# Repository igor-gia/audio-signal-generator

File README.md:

# AGP-S3: Dual-Channel Audio Generator & SD Player

[English](#english) | [Українська](#ukrainian) | [русский](#russian)

---

## English

**AGP-S3** is a compact dual-channel low-frequency DDS signal generator and audio player for lossless and high-resolution audio files. The device is based on an **ESP32-S3** microcontroller and a dedicated stereo **PCM5102A** DAC supporting up to 192 kHz / 24-bit audio.

The instrument is intended for testing, adjustment, and repair of audio equipment, including power amplifiers, loudspeakers, crossovers, equalizers, and other stages in the audio signal path.

---

## 📝 Author's Preface and Project Backstory

The idea for this device came from a practical problem encountered while building a home media centre based on an ESP32 and TPA3255, and assembling a custom 10-inch subwoofer using an Alpine driver and a TPA3255 monoblock in parallel bridge-tied load (PBTL) mode.

I had a portable FNIRSI DSO-TC4 on the bench, combining an oscilloscope and a signal generator. Both instruments share a common circuit ground. When adjusting an amplifier operating in bridge mode (BTL/PBTL), it is therefore not possible to apply a test signal to the input and measure the output with the oscilloscope at the same time: the test equipment would connect one output phase to ground.

The initial plan was to build a simple standalone sine-wave generator from the parts available. Since an **ESP32-S3 (N16R8)** was available, the project developed into a more complete instrument.

The result is a laboratory instrument covering two applications:
1. **Audio-equipment adjustment:** a dual-channel pure-tone generator, phase shifter, and test-noise source with galvanically isolated outputs for use with an oscilloscope.
2. **Audio playback:** a standalone player for lossless audio files that can be used as a reference source when evaluating audio signal paths.

Many DIY generators use the microcontroller's internal DACs or PWM output. Depending on the implementation, these can introduce significant distortion and unwanted spectral components. The **AGP-S3** uses a dedicated **PCM5102A** stereo DAC connected through I2S. The ESP32-S3 performs the phase and frequency calculations in real time.

---

## 🚀 Key Features

* **Dual-core operation:** Audio generation and I2S servicing run on one ESP32-S3 core, while the user interface, button handling, and SD-card access run on the other.
* **Audio output:** The PCM5102A provides an analogue output with sample rates up to 192 kHz and 24-bit samples.
* **Dual-channel DDS generator:** Frequency range from **1 Hz to 24,000 Hz**, with adjustment steps down to **0.1 Hz**. Supported waveforms: *Sine* and *Square*.
* **Phase control:** Manual phase adjustment between channels from $0^{\circ}$ to $360^{\circ}$ in $10^{\circ}$ steps, plus continuous automatic phase rotation at a user-defined speed.
* **Test noise and signals:** White-noise and pink-noise generators, plus a two-tone intermodulation-distortion (IMD) test mode.
* **Audio player:** Playback of **WAV, MP3, OGG, and FLAC** files from a FAT32 MicroSD card.
* **Built-in attenuator:** Two pairs of analogue RCA outputs: direct output (0 dB) and attenuated output (-20 dB) through a precision resistor divider for lower-level inputs.
* **Non-volatile settings:** Current settings and parameters are stored in the ESP32-S3 flash memory.

---

## 🛠 Technical Specifications

| Parameter | Value |
| :--- | :--- |
| **Microcontroller** | ESP32-S3-WROOM-1 (N16R8) |
| **DAC** | Texas Instruments PCM5102A (I2S) |
| **Resolution / Sample Rate** | 24-bit / up to 192 kHz |
| **Generator Frequency Range** | 1 Hz – 24,000 Hz |
| **Frequency Adjustment Step** | 0.1 Hz / 1 Hz / 10 Hz / 100 Hz / 1000 Hz |
| **Waveforms** | Sine, Square (Meander) |
| **Phase Adjustment** | $0^{\circ} - 360^{\circ}$ ($10^{\circ}$ step) + automatic rotation mode |
| **Noise Modes** | White Noise, Pink Noise, IMD (two-tone test) |
| **Supported Card Formats** | MicroSD, FAT32 (up to 32 GB) |
| **Supported Audio Formats** | MP3, WAV, FLAC, OGG |
| **Display** | OLED 0.96" (SSD1306, I2C, 128x64) |
| **Power Supply** | USB Type-C (5V) |

---

## 📦 Bill of Materials (BOM)

The main components required to build the device are listed below:

| Component | Description / Module | Qty |
| :--- | :--- | :--- |
| **Microcontroller** | ESP32-S3-DevKitC-1-N16R8V (or compatible board with 16MB Flash and 8MB PSRAM) | 1 pc. |
| **DAC** | PCM5102A DAC module with I2S interface | 1 pc. |
| **Display** | OLED 0.96" 128x64 module (SSD1306 driver, I2C interface) | 1 pc. |
| **Encoder** | EC11 incremental encoder with integrated push-button | 1 pc. |
| **Buttons** | Tactile push-buttons (12x12x7.5 mm) | 5 pcs. |
| **Card Reader** | MicroSD slot (TF-Card) wired for SD_MMC mode | 1 pc. |
| **Output Connectors** | Chassis-mount RCA jacks for the audio outputs | 4 pcs. |
| **Power Connector** | Chassis-mount USB Type-C female breakout for 5V power | 1 pc. |
| **Passives** | Resistors and capacitors specified in the schematic | 1 set |

---

## 📂 Repository Structure

```text
├── hardware/                 # Schematics and PCB layout
│    ├── kicad_project/       # Original project files in KiCad
│    ├── scheme_v2.pdf        # Complete schematic diagram in vector PDF format
│    └── scheme.png           # Schematic image for quick preview
├── src/                      # Source code for Arduino IDE (.ino)
├── docs/                     # Documentation and manuals
│    └── User manual.pdf      # Complete User Manual (in Russian)
├── images/                   # Photos and project media files
├── LICENSE                   # MIT License
└── README.md                 # Project overview (this file)
```
---

## 🔌 Hardware & Pinout

The complete schematic diagram is available in [`hardware/scheme_v2.pdf`](hardware/scheme_v2.pdf).

All controls (buttons and encoder) are wired with one terminal connected to a GPIO and the other to GND. The firmware uses the internal pull-up configuration: `INPUT_PULLUP`.

### ESP32-S3 Pin Mapping Table:

| GPIO | Function | Constant in `Config.h` / Settings |
| :--- | :--- | :--- |
| **GPIO 1** | 5V Power Detector (5V detected) | |
| **GPIO 2** | BCLK (PCM5102A DAC) | `BCLK_PIN` |
| **GPIO 4** | Tactile button "WAVE" | `PIN_BTN_5` |
| **GPIO 5** | Tactile button "RIGHT CH" | `PIN_BTN_3` |
| **GPIO 6** | Encoder Button (Enc Btn) | `PIN_ENC_BTN` |
| **GPIO 7** | Encoder Direction A (Enc+) | `PIN_ENC_A` |
| **GPIO 13**| Tactile button "LEFT CH" | `PIN_BTN_2` |
| **GPIO 14**| Tactile button "MODE" | `PIN_BTN_4` |
| **GPIO 15**| Encoder Direction B (Enc-) | `PIN_ENC_B` |
| **GPIO 16**| Tactile button "BOTH CH" | `PIN_BTN_1` |
| **GPIO 21**| TF-Card CMD (SD_MMC class) | `SD_MMC_CMD` |
| **GPIO 39**| SCL (SSD1306 Display) | `SCL_PIN` |
| **GPIO 40**| SDA (SSD1306 Display) | `SDA_PIN` |
| **GPIO 41**| LRCK / WS (PCM5102A DAC) | `LRCK_PIN` |
| **GPIO 42**| DIN / DOUT (PCM5102A DAC) | `DIN_PIN` |
| **GPIO 47**| TF-Card CLK (SD_MMC class) | `SD_MMC_CLK` |
| **GPIO 48**| TF-Card D0 (SD_MMC class) | `SD_MMC_D0` |

---

## 💻 Environment Setup & Flashing

To compile and upload the firmware to the ESP32-S3 through the development board's USB port, use the following **Arduino IDE** settings:

* **Board:** `ESP32S3 Dev Module`
* **Port:** Select the COM port of the connected device
* **USB CDC On Boot:** `Enabled` (for debug output in the Serial Monitor)
* **CPU Frequency:** `240MHz (WiFi/BT)`
* **Core Debug Level:** `None`
* **USB DFU On Boot:** `Disabled`
* **Erase All Flash Before Sketch Upload:** `Disabled`
* **Arduino Runs On:** `Core 0`
* **Events Run On:** `Core 1`
* **Flash Frequency:** `80MHz`
* **Flash Mode:** `QIO 80MHz`
* **Flash Size:** `16MB (128Mb)`
* **JTAG Adapter:** `Integrated USB JTAG`
* **Partition Scheme:** `16M Flash (3MB APP/9.9MB FATFS)`
* **PSRAM:** `OPI PSRAM`
* **Upload Mode:** `UART0 / Hardware CDC`
* **Upload Speed:** `921600`

---

## 🎮 Device Control (Quick Start)

### 1. Main Menu Navigation (Mode Selection)

When the device is powered on, or when the Main Menu is opened, the display shows the available operating modes.

* **Mode Selection (Moving the Highlight):** Use the **[LEFT]** and **[RIGHT]** buttons or turn the encoder. The selected mode is highlighted on the display.
* **Entering the Selected Mode:** Press **[BOTH]** to confirm and enter the highlighted mode.
* **Returning to the Main Menu:** From any active operating mode, press and hold **[MODE]**.

---

### 2. Setting the Frequency (in Generator Modes):

Frequency adjustment works as follows:
1. **Enter Frequency Edit Mode:** Press and **hold** one of the channel-selection buttons — **[LEFT]**, **[BOTH]**, or **[RIGHT]**.
2. **Select a Digit:** Press **[LEFT]** to move to the left and select a higher-order digit, or **[RIGHT]** to move to the right and select a lower-order digit. The selected position is marked by an underline cursor.
3. **Change the Digit Value:** Turn the encoder to increase or decrease the value of the selected digit.
4. **Exit Frequency Edit Mode:** Press **[BOTH]** to apply the changes and return to the normal display.

---

### 3. Operating Modes:

#### 📺 SCREEN 1. Wave Generator
This screen allows the left and right channels to be configured independently or together:
* The **[WAVE]** button cycles between **Sine** and **Square** waveforms.
* In the right-channel view (RIGHT), set the phase shift relative to the left channel from 0° to 360° in 10° steps, or enable automatic phase rotation at a speed from 1°/s to 360°/s.

#### 📺 SCREEN 2. Noises & Tests
Generates uncorrelated test signals and noise. Press any of the following buttons briefly to change the active signal type: [Left], [Both], [Right], or [Wave].
* **White Noise:** Approximately uniform spectral power density across the frequency range.
* **Pink Noise:** Spectral power density decreases by 3 dB per octave.
* **IMD (Intermodulation Distortion Test):** A two-tone signal for evaluating intermodulation distortion, with $f_1$ and $f_2$ mixed at user-defined amplitude ratios.

#### 📺 SCREEN 3. Audio Player
Plays WAV, MP3, OGG, and FLAC files from a FAT32 MicroSD card.
* Repeat options: repeat all files in the current folder (`Folder`) or repeat the current track (`Repeat`).
* Player controls:
  * **[LEFT]** — Previous track / rewind.
  * **[RIGHT]** — Next track / fast-forward.
  * **[BOTH]** — Start / stop playback.
  * **[WAVE]** — Pause playback.

#### 📺 SCREEN 4. Settings
Navigate through the settings list by turning the encoder or pressing [LEFT] / [RIGHT].
* To edit a setting, press the encoder button **[Encoder]** or **[BOTH]**. The cursor moves to the parameter value.
* Change the value by turning the encoder.
* Press the encoder button or **[BOTH]** again to save the setting in non-volatile memory.

**Some menu parameters:**
* `Phase Rot` (Automatic Phase Rotation): Rotation speed from 1°/s to 360°/s.
* `IMD f1`, `IMD f2`: Frequencies used for the two-tone intermodulation test.
* `IMD Amplit f1`, `IMD Amplit f2`: Amplitude ratios for the two tones; their sum must be 1.0, for example 0.8 and 0.2.
* `Player Mode`: Player repeat mode (`Folder` / `Repeat`).
* `Start Scr` (Startup Screen): Screen opened at startup (`Main`, `Waves`, `Noises`, `MP3`).

---

⚠️ **Important Note:** This Quick Start section covers the basic controls and the main operating modes. For the complete description of the operating modes, settings, and procedures, refer to the User Manual: [`docs/User manual.pdf`](docs/User%20manual.pdf) (currently available in Russian).

---

### Support
If you find this project useful and want to support the author, donations can be made using any of the following methods:

- **PayPal**: [gia@gia.org.ua] [Donate via PayPal](https://www.paypal.me)  
- **Ko-fi**: [Donate on Ko-fi](https://ko-fi.com/igorgimelfarb)  
- **Monobank**: Scan the QR code or use the link: [Support via Monobank](https://send.monobank.ua/jar/8HG6A3VPaW)

---

## ⚖️ License

This project is distributed under the **MIT License**. It may be used, modified, and distributed for commercial and non-commercial purposes, provided that the original copyright notice and author attribution are retained. See the [LICENSE](LICENSE) file for details.

---
*Project Author: Igor Gimelfarb (2026)*

---

###### Tags / Keywords: 
`esp32s3 audio generator`, `DDS signal generator DIY`, `PCM5102A I2S DAC`, `hi-res lossless player ESP32`, `audio testing tool`, `phase rotation generator`, `pink noise generator DIY`, `IMD test signal`, `BTL amplifier tuning`, `KiCad audio circuit`

---

[English](#english) | [Українська](#ukrainian) | [русский](#russian)

---

## Ukrainian

# AGP-S3: Dual-Channel Audio Generator & SD Player

**AGP-S3** — компактний двоканальний низькочастотний DDS-генератор сигналів і аудіоплеєр для відтворення аудіофайлів без втрат та у форматах високої роздільності. Пристрій побудований на базі мікроконтролера **ESP32-S3** та спеціалізованого стерео-ЦАП **PCM5102A** з підтримкою до 192 кГц / 24 біт.

Прилад призначений для тестування, налаштування та ремонту аудіоапаратури, зокрема підсилювачів потужності, акустичних систем, кросоверів, еквалайзерів та інших ланок звукового тракту.

---

## 📝 Передмова автора та передісторія проєкту

Ідея створення цього приладу виникла з практичної задачі. Під час побудови домашнього медіацентру на базі ESP32 і TPA3255 та складання кастомного 10-дюймового сабвуфера з динаміком Alpine і моноблоком TPA3255 у режимі паралельного мостового навантаження (PBTL) я зіткнувся з проблемою налаштування аудіосистеми.

На робочому столі був портативний FNIRSI DSO-TC4, який поєднує осцилограф і генератор сигналів. Обидва прилади мають спільну схемну землю. Під час налаштування підсилювача у мостовому режимі (BTL/PBTL) неможливо одночасно подати тестовий сигнал на вхід і вимірювати вихід осцилографом: вимірювальний прилад з'єднає одну з вихідних фаз із землею.

Спочатку планувалося зібрати простий автономний генератор синусоїдального сигналу з доступних деталей. Оскільки під рукою був **ESP32-S3 (N16R8)**, проєкт переріс початковий задум.

У результаті вийшов лабораторний прилад для двох основних задач:
1. **Налаштування аудіоапаратури:** двоканальний генератор чистих тонів, фазообертач і генератор тестових шумів із гальванічно розв'язаними виходами для роботи з осцилографом.
2. **Відтворення аудіо:** автономний програвач аудіофайлів без втрат, який можна використовувати як еталонне джерело під час оцінювання звукових трактів.

У багатьох аматорських генераторах використовуються внутрішні ЦАП мікроконтролера або ШІМ-вихід. Залежно від реалізації це може призводити до значних спотворень і небажаних спектральних складових. В **AGP-S3** використовується спеціалізований стерео-ЦАП **PCM5102A**, підключений через I2S. ESP32-S3 виконує розрахунок фази та частоти в реальному часі.

---

## 🚀 Ключові особливості

* **Робота з двома ядрами:** генерація звуку та обслуговування шини I2S виконуються на одному ядрі ESP32-S3, а графічний інтерфейс, обробка кнопок і робота з SD-картою — на іншому.
* **Аудіовихід:** PCM5102A забезпечує аналоговий сигнал із частотою дискретизації до 192 кГц і 24-бітними відліками.
* **Двоканальний DDS-генератор:** діапазон частот від **1 Гц до 24 000 Гц**, крок налаштування — до **0,1 Гц**. Підтримувані форми сигналу: *Синусоїда* та *Меандр*.
* **Керування фазою:** ручне встановлення зсуву фази між каналами від $0^{\circ}$ до $360^{\circ}$ із кроком $10^{\circ}$, а також безперервне автоматичне обертання фази із заданою швидкістю.
* **Тестові шуми та сигнали:** генератори білого й рожевого шуму, а також режим двотонального тесту інтермодуляційних спотворень (IMD).
* **Аудіоплеєр:** відтворення файлів **WAV, MP3, OGG і FLAC** із карти MicroSD у форматі FAT32.
* **Вбудований атенюатор:** дві пари аналогових виходів RCA: прямий вихід (0 дБ) і вихід із послабленням -20 дБ через прецизійний резистивний дільник для входів із нижчим рівнем сигналу.
* **Енергонезалежні налаштування:** поточні налаштування та параметри зберігаються у флеш-пам'яті ESP32-S3.

---

## 🛠 Технічні характеристики

| Параметр | Значення |
| :--- | :--- |
| **Мікроконтролер** | ESP32-S3-WROOM-1 (N16R8) |
| **ЦАП (DAC)** | Texas Instruments PCM5102A (I2S) |
| **Розрядність / Частота дискретизації** | 24 біт / до 192 кГц |
| **Діапазон частот генератора** | 1 Гц – 24 000 Гц |
| **Крок налаштування частоти** | 0,1 Гц / 1 Гц / 10 Гц / 100 Гц / 1000 Гц |
| **Форми сигналу** | Синусоїда (Sine), Меандр (Square) |
| **Регулювання фази** | $0^{\circ} - 360^{\circ}$ (крок $10^{\circ}$) + автоматичне обертання |
| **Режими шумів** | Білий шум, рожевий шум, IMD (двотональний тест) |
| **Підтримувані формати карт пам'яті** | MicroSD, FAT32 (до 32 ГБ) |
| **Підтримувані аудіоформати** | MP3, WAV, FLAC, OGG |
| **Дисплей** | OLED 0.96" (SSD1306, I2C, 128x64) |
| **Живлення** | USB Type-C (5 В) |

---

## 📦 Список компонентів (BOM)

Основні компоненти, необхідні для складання пристрою:

| Компонент | Опис / Модуль | Кількість |
| :--- | :--- | :--- |
| **Мікроконтролер** | ESP32-S3-DevKitC-1-N16R8V (або сумісна плата з 16MB Flash та 8MB PSRAM) | 1 шт. |
| **ЦАП** | Модуль ЦАП PCM5102A з інтерфейсом I2S | 1 шт. |
| **Дисплей** | Модуль OLED 0.96" 128x64 (драйвер SSD1306, інтерфейс I2C) | 1 шт. |
| **Енкодер** | Інкрементальний енкодер EC11 із вбудованою кнопкою | 1 шт. |
| **Кнопки** | Тактові кнопки 12x12x7.5 мм | 5 шт. |
| **Кардридер** | Слот MicroSD (TF-Card) для роботи в режимі SD_MMC | 1 шт. |
| **Вихідні роз'єми** | Панельні гнізда RCA для аудіовиходів | 4 шт. |
| **Роз'єм живлення** | Панельний роз'єм USB Type-C для живлення 5 В | 1 шт. |
| **Пасивні елементи** | Резистори та конденсатори згідно зі схемою | 1 компл. |

---

## 📂 Структура репозиторію

```text
├── hardware/                 # Схемотехніка та друкована плата
│    ├── kicad_project/       # Вихідні файли проєкту в KiCad
│    ├── scheme_v2.pdf        # Повна принципова схема у векторному форматі PDF
│    └── scheme.png           # Зображення принципової схеми для швидкого перегляду
├── src/                      # Вихідний код проєкту для Arduino IDE (.ino)
├── docs/                     # Документація та посібники
│    └── User manual.pdf      # Повний посібник користувача (російською мовою)
├── images/                   # Фотографії та медіафайли проєкту
├── LICENSE                   # Ліцензія MIT
└── README.md                 # Опис проєкту (цей файл)
```
---

## 🔌 Схемотехніка та розпиновка пристрою

Повна принципова схема пристрою у форматі PDF знаходиться у файлі [`hardware/scheme_v2.pdf`](hardware/scheme_v2.pdf).

Усі органи керування (кнопки та енкодер) підключені так: один вивід підключений до GPIO, другий — до GND. У прошивці використовується внутрішня підтяжка входу: `INPUT_PULLUP`.

### Таблиця підключення периферії до ESP32-S3:

| GPIO | Призначення | Константа в `Config.h` / Налаштування |
| :--- | :--- | :--- |
| **GPIO 1** | Детектор живлення 5 В (5V detected) | |
| **GPIO 2** | BCLK (ЦАП PCM5102A) | `BCLK_PIN` |
| **GPIO 4** | Тактова кнопка «WAVE» | `PIN_BTN_5` |
| **GPIO 5** | Тактова кнопка «RIGHT CH» | `PIN_BTN_3` |
| **GPIO 6** | Кнопка енкодера (Enc Btn) | `PIN_ENC_BTN` |
| **GPIO 7** | Напрямок енкодера (Enc+) | `PIN_ENC_A` |
| **GPIO 13**| Тактова кнопка «LEFT CH» | `PIN_BTN_2` |
| **GPIO 14**| Тактова кнопка «MODE» | `PIN_BTN_4` |
| **GPIO 15**| Напрямок енкодера (Enc-) | `PIN_ENC_B` |
| **GPIO 16**| Тактова кнопка «BOTH CH» | `PIN_BTN_1` |
| **GPIO 21**| TF-Card CMD (клас SD_MMC) | `SD_MMC_CMD` |
| **GPIO 39**| SCL (дисплей SSD1306) | `SCL_PIN` |
| **GPIO 40**| SDA (дисплей SSD1306) | `SDA_PIN` |
| **GPIO 41**| LRCK / WS (ЦАП PCM5102A) | `LRCK_PIN` |
| **GPIO 42**| DIN / DOUT (ЦАП PCM5102A) | `DIN_PIN` |
| **GPIO 47**| TF-Card CLK (клас SD_MMC) | `SD_MMC_CLK` |
| **GPIO 48**| TF-Card D0 (клас SD_MMC) | `SD_MMC_D0` |

---

## 💻 Налаштування середовища та прошивка

Для компіляції та завантаження прошивки в ESP32-S3 через USB-роз'єм плати розробника використовуйте такі параметри **Arduino IDE**:

* **Board (Плата):** `ESP32S3 Dev Module`
* **Port (Порт):** Виберіть COM-порт підключеного пристрою
* **USB CDC On Boot:** `Enabled` (для виведення повідомлень налагодження в Serial Monitor)
* **CPU Frequency:** `240MHz (WiFi/BT)`
* **Core Debug Level:** `None`
* **USB DFU On Boot:** `Disabled`
* **Erase All Flash Before Sketch Upload:** `Disabled`
* **Arduino Runs On:** `Core 0`
* **Events Run On:** `Core 1`
* **Flash Frequency:** `80MHz`
* **Flash Mode:** `QIO 80MHz`
* **Flash Size:** `16MB (128Mb)`
* **JTAG Adapter:** `Integrated USB JTAG`
* **Partition Scheme:** `16M Flash (3MB APP/9.9MB FATFS)`
* **PSRAM:** `OPI PSRAM`
* **Upload Mode:** `UART0 / Hardware CDC`
* **Upload Speed:** `921600`

---

## 🎮 Керування пристроєм (Швидкий старт)

### 1. Навігація на Головному екрані (Вибір режиму)

Після увімкнення приладу або переходу на Головний екран дисплей показує список доступних режимів роботи.

* **Вибір режиму (переміщення підсвічування):** Використовуйте кнопки **[LEFT]**, **[RIGHT]** або обертайте енкодер. Вибраний режим буде підсвічено на дисплеї.
* **Вхід у вибраний режим:** Натисніть **[BOTH]**, щоб підтвердити вибір і відкрити режим.
* **Повернення на Головний екран:** Із будь-якого активного режиму натисніть і утримуйте **[MODE]**.

---

### 2. Налаштування частоти (у режимах генератора):

Налаштування частоти виконується так:
1. **Вхід у режим редагування частоти:** Натисніть і **утримуйте** одну з кнопок вибору каналів — **[LEFT]**, **[BOTH]** або **[RIGHT]**.
2. **Вибір розряду:** Натискайте **[LEFT]**, щоб перейти ліворуч і вибрати старший розряд, або **[RIGHT]**, щоб перейти праворуч і вибрати молодший розряд. Вибрана позиція позначається курсором-підкресленням.
3. **Зміна значення розряду:** Обертайте енкодер, щоб збільшити або зменшити значення вибраного розряду.
4. **Вихід із режиму редагування частоти:** Натисніть **[BOTH]**, щоб застосувати зміни та повернутися до звичайного відображення.

---

### 3. Режими роботи приладу:

#### ЕКРАН 1. Генератор сигналів (Waves)
Цей екран дає змогу незалежно або спільно налаштовувати лівий і правий канали:
* Кнопка **[WAVE]** почергово вибирає **синусоїду** або **меандр**.
* На екрані правого каналу (RIGHT) можна встановити зсув фази відносно лівого каналу від 0° до 360° із кроком 10° або ввімкнути автоматичне обертання фази зі швидкістю від 1°/с до 360°/с.

#### ЕКРАН 2. Шуми та тести (Noises)
Генерує некорельовані тестові сигнали та шуми. Для вибору типу сигналу коротко натискайте одну з кнопок: [Left], [Both], [Right] або [Wave]:
* **White Noise (білий шум):** приблизно рівномірна спектральна щільність потужності в діапазоні частот.
* **Pink Noise (рожевий шум):** спад спектральної щільності потужності на 3 дБ на октаву.
* **IMD (Intermodulation Distortion Test):** двотональний сигнал для оцінювання інтермодуляційних спотворень, у якому $f_1$ та $f_2$ змішуються в заданих співвідношеннях амплітуд.

#### ЕКРАН 3. Аудіоплеєр (Player)
Відтворює файли WAV, MP3, OGG і FLAC із карти MicroSD у форматі FAT32.
* Режими повторення: усі файли поточної папки (`Folder`) або поточний трек (`Repeat`).
* Керування плеєром:
  * **[LEFT]** — попередній трек / перемотування назад.
  * **[RIGHT]** — наступний трек / перемотування вперед.
  * **[BOTH]** — початок / зупинка відтворення.
  * **[WAVE]** — пауза відтворення.

#### ЕКРАН 4. Налаштування (Settings)
Переміщуйтеся списком параметрів обертанням енкодера або натисканням [LEFT] / [RIGHT].
* Для редагування параметра натисніть кнопку енкодера **[Encoder]** або **[BOTH]**. Курсор переміститься до значення параметра.
* Змініть значення обертанням енкодера.
* Натисніть кнопку енкодера або **[BOTH]** ще раз, щоб зберегти налаштування в енергонезалежній пам'яті.

**Деякі параметри меню:**
* `Phase Rot` (Автоматичне обертання фази): швидкість від 1°/с до 360°/с.
* `IMD f1`, `IMD f2`: частоти для двотонального тесту інтермодуляційних спотворень.
* `IMD Amplit f1`, `IMD Amplit f2`: співвідношення амплітуд двох тонів; сума має дорівнювати 1,0, наприклад 0,8 і 0,2.
* `Player Mode`: режим повторення плеєра (`Folder` / `Repeat`).
* `Start Scr` (Стартовий екран): екран, який відкривається під час запуску (`Main`, `Waves`, `Noises`, `MP3`).

---

⚠️ **Важлива примітка:** У цьому розділі «Швидкий старт» описано основні елементи керування та режими роботи. Повний опис режимів, налаштувань і процедур наведено в посібнику користувача: [`docs/User manual.pdf`](docs/User%20manual.pdf) (нині доступний російською мовою).

---

### Підтримка
Якщо цей проєкт став вам у пригоді, підтримати автора можна одним із таких способів:

- **PayPal**: [gia@gia.org.ua] [Donate via PayPal](https://www.paypal.me)  
- **Ko-fi**: [Donate on Ko-fi](https://ko-fi.com/igorgimelfarb)  
- **Monobank**: відскануйте QR-код або скористайтеся посиланням: [Підтримати через Monobank](https://send.monobank.ua/jar/8HG6A3VPaW)

---

## ⚖️ Ліцензія

Цей проєкт поширюється за ліцензією **MIT**. Його можна використовувати, змінювати та поширювати в комерційних і некомерційних цілях за умови збереження початкового повідомлення про авторські права та зазначення автора. Подробиці наведено у файлі [LICENSE](LICENSE).

---
*Автор проєкту: Ігор Гімельфарб (2026 р.)*

---

###### Теги / Ключові слова:
`генератор звукових частот ESP32`, `DDS генератор сигналів`, `ЦАП PCM5102A I2S`, `аудіоплеєр на ESP32-S3`, `вимірювання спотворень підсилювача`, `генератор рожевого шуму`, `тестування мостових підсилювачів`, `радіоаматорські прилади DIY`

---

[English](#english) | [Українська](#ukrainian) | [русский](#russian)

---

## russian

# AGP-S3: Dual-Channel Audio Generator & SD Player

**AGP-S3** — компактный двухканальный низкочастотный DDS-генератор сигналов и аудиопроигрыватель для файлов без потерь и файлов высокого разрешения. Устройство построено на базе микроконтроллера **ESP32-S3** и специализированного стерео-ЦАП **PCM5102A** с поддержкой до 192 кГц / 24 бит.

Прибор предназначен для тестирования, настройки и ремонта аудиоаппаратуры, включая усилители мощности, акустические системы, кроссоверы, эквалайзеры и другие звенья звукового тракта.

---

## 📝 Предисловие автора и предыстория проекта

Идея создания этого прибора возникла из практической задачи. Во время создания домашнего медиацентра на базе ESP32 и TPA3255 и сборки кастомного 10-дюймового сабвуфера с динамиком Alpine и моноблоком TPA3255 в режиме параллельной мостовой нагрузки (PBTL) я столкнулся с проблемой настройки аудиосистемы.

На рабочем столе был портативный FNIRSI DSO-TC4, совмещающий осциллограф и генератор сигналов. Оба прибора имеют общую схемную землю. При настройке усилителя в мостовом режиме (BTL/PBTL) невозможно одновременно подать тестовый сигнал на вход и измерять выход осциллографом: измерительный прибор соединит одну из выходных фаз с землей.

Сначала планировалось собрать простой автономный генератор синусоидального сигнала из доступных деталей. Поскольку под рукой был **ESP32-S3 (N16R8)**, проект вышел за рамки первоначальной задачи.

В результате получился лабораторный прибор для двух основных задач:
1. **Настройка аудиоаппаратуры:** двухканальный генератор чистых тонов, фазовращатель и генератор тестовых шумов с гальванически развязанными выходами для работы с осциллографом.
2. **Воспроизведение аудио:** автономный проигрыватель аудиофайлов без потерь, который можно использовать как эталонный источник при оценке звуковых трактов.

Во многих любительских генераторах используются встроенные ЦАП микроконтроллера или ШИМ-выход. В зависимости от реализации это может приводить к значительным искажениям и появлению нежелательных спектральных составляющих. В **AGP-S3** используется специализированный стерео-ЦАП **PCM5102A**, подключенный по шине I2S. ESP32-S3 выполняет расчёт фазы и частоты в реальном времени.

---

## 🚀 Ключевые особенности

* **Работа с двумя ядрами:** генерация звука и обслуживание шины I2S выполняются на одном ядре ESP32-S3, а графический интерфейс, обработка кнопок и работа с SD-картой — на другом.
* **Аудиовыход:** PCM5102A обеспечивает аналоговый сигнал с частотой дискретизации до 192 кГц и 24-битными отсчётами.
* **Двухканальный DDS-генератор:** диапазон частот от **1 Гц до 24 000 Гц**, шаг настройки — до **0.1 Гц**. Поддерживаемые формы сигнала: *Синусоида* и *Меандр*.
* **Управление фазой:** ручная установка сдвига фазы между каналами от $0^{\circ}$ до $360^{\circ}$ с шагом $10^{\circ}$, а также непрерывное автоматическое вращение фазы с заданной скоростью.
* **Тестовые шумы и сигналы:** генераторы белого и розового шума, а также режим двухтонального теста интермодуляционных искажений (IMD).
* **Аудиопроигрыватель:** воспроизведение файлов **WAV, MP3, OGG и FLAC** с карты MicroSD в формате FAT32.
* **Встроенный аттенюатор:** две пары аналоговых выходов RCA: прямой выход (0 дБ) и выход с ослаблением -20 дБ через прецизионный резистивный делитель для входов с более низким уровнем сигнала.
* **Энергонезависимые настройки:** текущие настройки и параметры сохраняются во флеш-памяти ESP32-S3.

---

## 🛠 Технические характеристики

| Параметр | Значение |
| :--- | :--- |
| **Микроконтроллер** | ESP32-S3-WROOM-1 (N16R8) |
| **ЦАП (DAC)** | Texas Instruments PCM5102A (I2S) |
| **Разрядность / Частота дискретизации** | 24 бит / до 192 кГц |
| **Диапазон частот генератора** | 1 Гц – 24 000 Гц |
| **Шаг настройки частоты** | 0.1 Гц / 1 Гц / 10 Гц / 100 Гц / 1000 Гц |
| **Формы сигнала** | Синусоида (Sine), Меандр (Square) |
| **Регулировка фазы** | $0^{\circ} - 360^{\circ}$ (шаг $10^{\circ}$) + автоматическое вращение |
| **Режимы шумов** | Белый шум, розовый шум, IMD (двухтональный тест) |
| **Поддерживаемые форматы карт памяти** | MicroSD, FAT32 (до 32 ГБ) |
| **Поддерживаемые аудиоформаты** | MP3, WAV, FLAC, OGG |
| **Дисплей** | OLED 0.96" (SSD1306, I2C, 128x64) |
| **Питание** | USB Type-C (5 В) |

---

## 📦 Список компонентов (BOM)

Основные компоненты, необходимые для сборки устройства:

| Компонент | Описание / Модуль | Кол-во |
| :--- | :--- | :--- |
| **Микроконтроллер** | ESP32-S3-DevKitC-1-N16R8V (или совместимая плата с 16MB Flash и 8MB PSRAM) | 1 шт. |
| **ЦАП** | Модуль ЦАП PCM5102A с интерфейсом I2S | 1 шт. |
| **Дисплей** | Модуль OLED 0.96" 128x64 (драйвер SSD1306, интерфейс I2C) | 1 шт. |
| **Энкодер** | Инкрементальный энкодер EC11 со встроенной кнопкой | 1 шт. |
| **Кнопки** | Тактовые кнопки 12x12x7.5 мм | 5 шт. |
| **Кардридер** | Слот MicroSD (TF-Card) для работы в режиме SD_MMC | 1 шт. |
| **Выходные разъемы** | Панельные гнезда RCA для аудиовыходов | 4 шт. |
| **Разъем питания** | Панельный разъем USB Type-C для питания 5 В | 1 шт. |
| **Пассивные элементы** | Резисторы и конденсаторы согласно схеме | 1 компл. |

---

## 📂 Структура репозитория

```text
├── hardware/                 # Схемотехника и печатная плата
│    ├── kicad_project/       # Исходные файлы проекта в KiCad
│    ├── scheme_v2.pdf        # Полная принципиальная схема в векторном формате PDF
│    └── scheme.png           # Изображение принципиальной схемы для быстрого просмотра
├── src/                      # Исходный код проекта для Arduino IDE (.ino)
├── docs/                     # Документация и руководства
│    └── User manual.pdf      # Полное руководство пользователя на русском языке
├── images/                   # Фотографии и медиафайлы проекта
├── LICENSE                   # Лицензия MIT
└── README.md                 # Описание проекта (этот файл)
```
---

## 🔌 Схемотехника и распиновка устройства

Полная принципиальная схема устройства в формате PDF находится в файле [`hardware/scheme_v2.pdf`](hardware/scheme_v2.pdf).

Все органы управления (кнопки и энкодер) подключены так: один вывод подключён к GPIO, второй — к GND. В прошивке используется внутренняя подтяжка входа: `INPUT_PULLUP`.

### Таблица подключения периферии к ESP32-S3:

| GPIO | Назначение | Константа в `Config.h` / Настройки |
| :--- | :--- | :--- |
| **GPIO 1** | Детектор питания 5 В (5V detected) | |
| **GPIO 2** | BCLK (ЦАП PCM5102A) | `BCLK_PIN` |
| **GPIO 4** | Тактовая кнопка «WAVE» | `PIN_BTN_5` |
| **GPIO 5** | Тактовая кнопка «RIGHT CH» | `PIN_BTN_3` |
| **GPIO 6** | Кнопка энкодера (Enc Btn) | `PIN_ENC_BTN` |
| **GPIO 7** | Направление энкодера (Enc+) | `PIN_ENC_A` |
| **GPIO 13**| Тактовая кнопка «LEFT CH» | `PIN_BTN_2` |
| **GPIO 14**| Тактовая кнопка «MODE» | `PIN_BTN_4` |
| **GPIO 15**| Направление энкодера (Enc-) | `PIN_ENC_B` |
| **GPIO 16**| Тактовая кнопка «BOTH CH» | `PIN_BTN_1` |
| **GPIO 21**| TF-Card CMD (класс SD_MMC) | `SD_MMC_CMD` |
| **GPIO 39**| SCL (дисплей SSD1306) | `SCL_PIN` |
| **GPIO 40**| SDA (дисплей SSD1306) | `SDA_PIN` |
| **GPIO 41**| LRCK / WS (ЦАП PCM5102A) | `LRCK_PIN` |
| **GPIO 42**| DIN / DOUT (ЦАП PCM5102A) | `DIN_PIN` |
| **GPIO 47**| TF-Card CLK (класс SD_MMC) | `SD_MMC_CLK` |
| **GPIO 48**| TF-Card D0 (класс SD_MMC) | `SD_MMC_D0` |

---

## 💻 Настройка среды и прошивка

Для компиляции и загрузки прошивки в ESP32-S3 через USB-разъем платы разработки используйте следующие параметры **Arduino IDE**:

* **Board (Плата):** `ESP32S3 Dev Module`
* **Port (Порт):** Выберите COM-порт подключенного устройства
* **USB CDC On Boot:** `Enabled` (для вывода сообщений отладки в Serial Monitor)
* **CPU Frequency:** `240MHz (WiFi/BT)`
* **Core Debug Level:** `None`
* **USB DFU On Boot:** `Disabled`
* **Erase All Flash Before Sketch Upload:** `Disabled`
* **Arduino Runs On:** `Core 0`
* **Events Run On:** `Core 1`
* **Flash Frequency:** `80MHz`
* **Flash Mode:** `QIO 80MHz`
* **Flash Size:** `16MB (128Mb)`
* **JTAG Adapter:** `Integrated USB JTAG`
* **Partition Scheme:** `16M Flash (3MB APP/9.9MB FATFS)`
* **PSRAM:** `OPI PSRAM`
* **Upload Mode:** `UART0 / Hardware CDC`
* **Upload Speed:** `921600`

---

## 🎮 Управление устройством (Быстрый старт)

### 1. Навигация на Главном экране (Выбор режима)

При включении прибора или переходе на Главный экран дисплей показывает список доступных режимов работы.

* **Выбор режима (перемещение подсветки):** Используйте кнопки **[LEFT]**, **[RIGHT]** или вращайте энкодер. Выбранный режим будет подсвечен на дисплее.
* **Вход в выбранный режим:** Нажмите **[BOTH]**, чтобы подтвердить выбор и открыть режим.
* **Возврат на Главный экран:** Из любого активного режима нажмите и удерживайте **[MODE]**.

---

### 2. Настройка частоты (в режимах генератора):

Настройка частоты выполняется следующим образом:
1. **Вход в режим редактирования частоты:** Нажмите и **удерживайте** одну из кнопок выбора каналов — **[LEFT]**, **[BOTH]** или **[RIGHT]**.
2. **Выбор разряда:** Нажимайте **[LEFT]**, чтобы перейти влево и выбрать старший разряд, или **[RIGHT]**, чтобы перейти вправо и выбрать младший разряд. Выбранная позиция отмечается курсором-подчеркиванием.
3. **Изменение значения разряда:** Вращайте энкодер, чтобы увеличить или уменьшить значение выбранного разряда.
4. **Выход из режима редактирования частоты:** Нажмите **[BOTH]**, чтобы применить изменения и вернуться к обычному отображению.

---

### 3. Режимы работы прибора:

#### ЭКРАН 1. Генератор сигналов (Waves)
Этот экран позволяет настраивать левый и правый каналы независимо или одновременно:
* Кнопка **[WAVE]** поочередно выбирает **синусоиду** или **меандр**.
* На экране правого канала (RIGHT) можно установить сдвиг фазы относительно левого канала от 0° до 360° с шагом 10° или включить автоматическое вращение фазы со скоростью от 1°/с до 360°/с.

#### ЭКРАН 2. Шумы и тесты (Noises)
Генерирует некоррелированные тестовые сигналы и шумы. Для выбора типа сигнала кратко нажимайте одну из кнопок: [Left], [Both], [Right] или [Wave]:
* **White Noise (белый шум):** приблизительно равномерная спектральная плотность мощности в диапазоне частот.
* **Pink Noise (розовый шум):** спад спектральной плотности мощности на 3 дБ на октаву.
* **IMD (Intermodulation Distortion Test):** двухтональный сигнал для оценки интермодуляционных искажений, в котором $f_1$ и $f_2$ смешиваются в заданных соотношениях амплитуд.

#### ЭКРАН 3. Аудиопроигрыватель (Player)
Воспроизводит файлы WAV, MP3, OGG и FLAC с карты MicroSD в формате FAT32.
* Режимы повтора: все файлы текущей папки (`Folder`) или текущий трек (`Repeat`).
* Управление проигрывателем:
  * **[LEFT]** — предыдущий трек / перемотка назад.
  * **[RIGHT]** — следующий трек / перемотка вперед.
  * **[BOTH]** — начало / остановка воспроизведения.
  * **[WAVE]** — пауза воспроизведения.

#### ЭКРАН 4. Настройки (Settings)
Перемещайтесь по списку параметров вращением энкодера или нажатием [LEFT] / [RIGHT].
* Для редактирования параметра нажмите кнопку энкодера **[Encoder]** или **[BOTH]**. Курсор перейдет к значению параметра.
* Измените значение вращением энкодера.
* Нажмите кнопку энкодера или **[BOTH]** еще раз, чтобы сохранить настройку в энергонезависимой памяти.

**Некоторые параметры меню:**
* `Phase Rot` (Автоматическое вращение фазы): скорость от 1°/с до 360°/с.
* `IMD f1`, `IMD f2`: частоты для двухтонального теста интермодуляционных искажений.
* `IMD Amplit f1`, `IMD Amplit f2`: соотношения амплитуд двух тонов; сумма должна быть равна 1,0, например 0,8 и 0,2.
* `Player Mode`: режим повтора проигрывателя (`Folder` / `Repeat`).
* `Start Scr` (Стартовый экран): экран, открываемый при запуске (`Main`, `Waves`, `Noises`, `MP3`).

---

⚠️ **Важное примечание:** В разделе «Быстрый старт» описаны основные элементы управления и режимы работы. Полное описание режимов, настроек и процедур приведено в руководстве пользователя: [`docs/User manual.pdf`](docs/User%20manual.pdf) (в настоящее время доступно на русском языке).

---

### Поддержка
Если этот проект оказался вам полезен, поддержать автора можно одним из следующих способов:

- **PayPal**: [gia@gia.org.ua] [Donate via PayPal](https://www.paypal.me)  
- **Ko-fi**: [Donate on Ko-fi](https://ko-fi.com/igorgimelfarb)  
- **Monobank**: отсканируйте QR-код или воспользуйтесь ссылкой: [Поддержать через Monobank](https://send.monobank.ua/jar/8HG6A3VPaW)

---

## ⚖️ Лицензия

Этот проект распространяется по лицензии **MIT**. Его можно использовать, изменять и распространять в коммерческих и некоммерческих целях при условии сохранения исходного уведомления об авторских правах и указания автора. Подробности приведены в файле [LICENSE](LICENSE).

---
*Автор проекта: Игорь Гимельфарб (2026 г.)*

---

###### Теги / Ключевые слова:
`генератор звуковых частот ESP32`, `DDS генератор сигналов`, `ЦАП PCM5102A I2S`, `аудиоплеер на ESP32-S3`, `измерение искажений усилителя`, `генератор розового шума`, `тестирование мостовых усилителей`, `радиолюбительские приборы DIY`

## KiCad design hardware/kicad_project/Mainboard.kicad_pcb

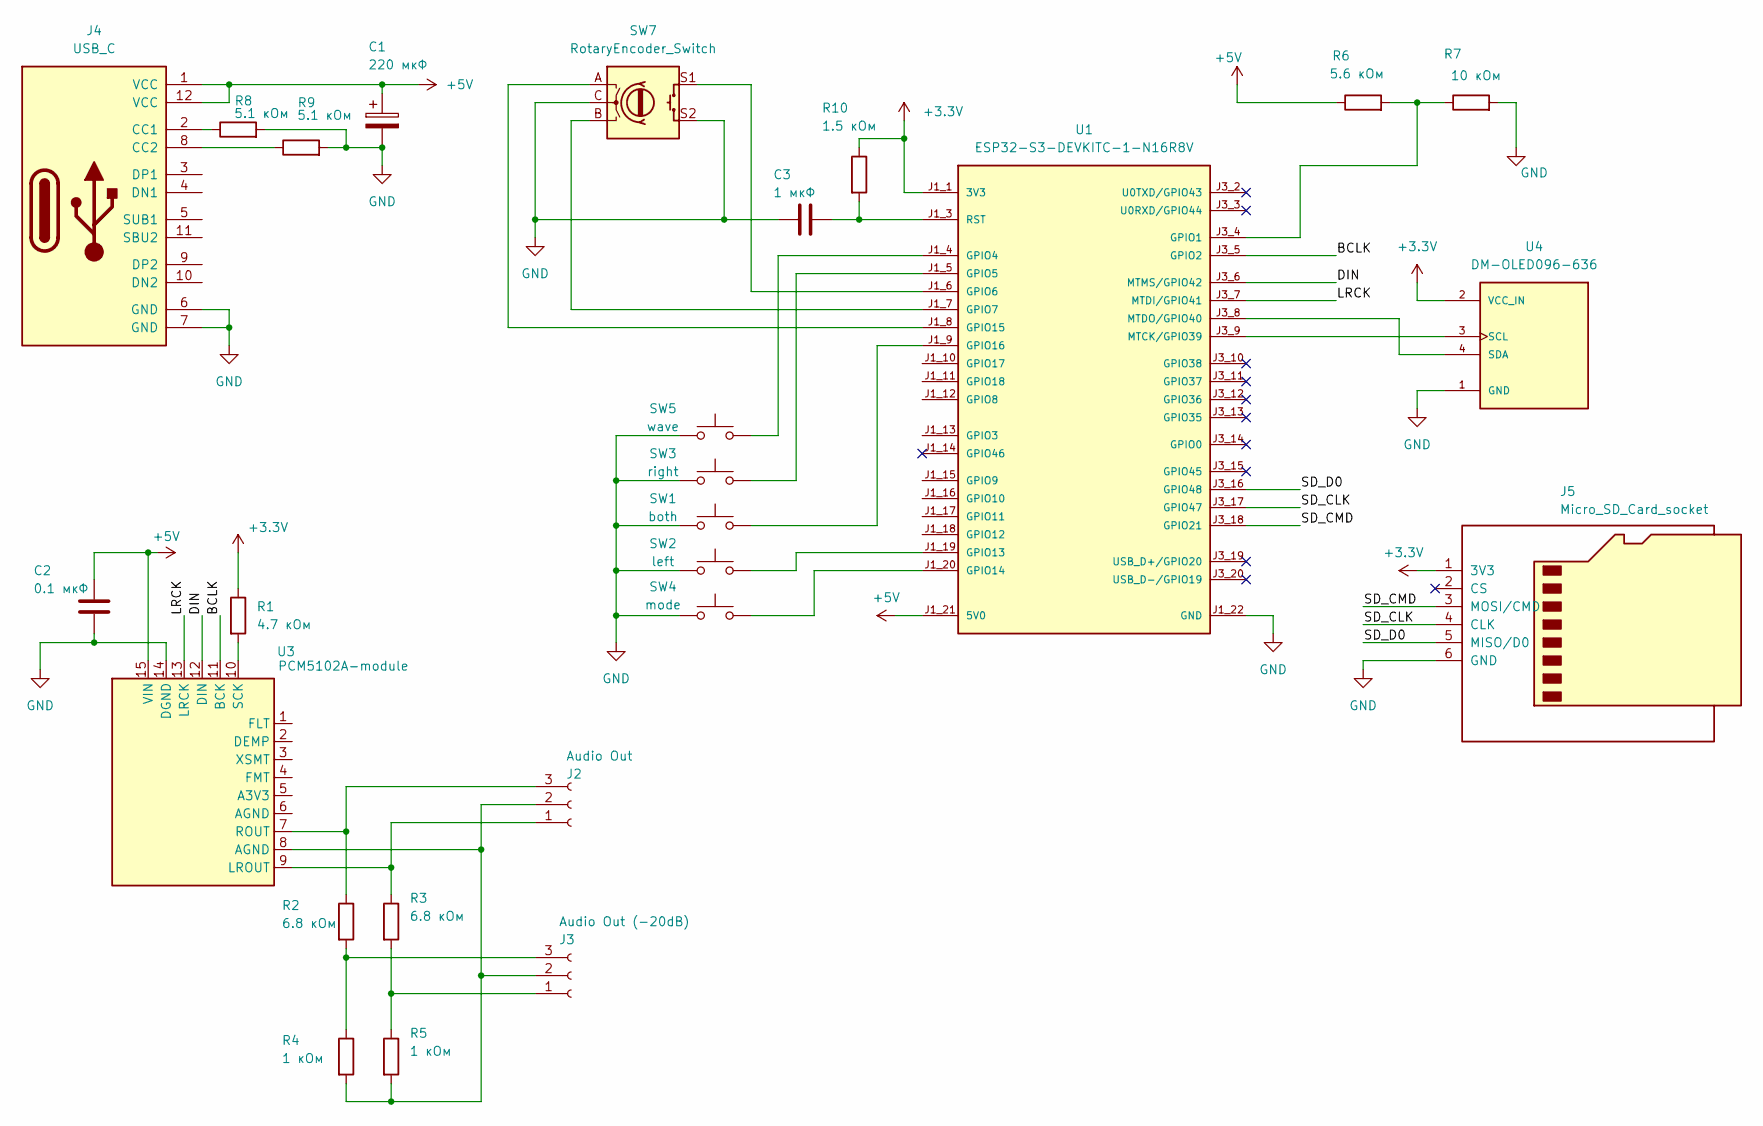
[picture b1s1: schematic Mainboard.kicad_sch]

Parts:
C1: 220 мкФ; CP_Radial_D6.3mm_P2.50mm
C2: 0.1 мкФ; C_Disc_D5.0mm_W2.5mm_P2.50mm
C3: 1 мкФ; C_Disc_D5.0mm_W2.5mm_P2.50mm
J2: Audio Out; JST_XH_B3B-XH-A_1x03_P2.50mm_Vertical
J3: Audio Out (-20dB); JST_XH_B3B-XH-A_1x03_P2.50mm_Vertical
J4: USB_C; USB-C-DEV
J5: Micro_SD_Card_socket
R1: 4.7 кОм; R_Axial_DIN0207_L6.3mm_D2.5mm_P7.62mm_Horizontal
R2, R3: 6.8 кОм; R_Axial_DIN0207_L6.3mm_D2.5mm_P7.62mm_Horizontal
R4, R5: 1 кОм; R_Axial_DIN0207_L6.3mm_D2.5mm_P7.62mm_Horizontal
R6: 5.6 кОм; R_Axial_DIN0207_L6.3mm_D2.5mm_P7.62mm_Horizontal
R7: 10 кОм; R_Axial_DIN0207_L6.3mm_D2.5mm_P7.62mm_Horizontal
R8, R9: 5.1 кОм; R_Axial_DIN0207_L6.3mm_D2.5mm_P7.62mm_Horizontal
R10: 1.5 кОм; R_Axial_DIN0207_L6.3mm_D2.5mm_P7.62mm_Horizontal
SW1: both; SW_SPST_12x12
SW2: left; SW_SPST_12x12
SW3: right; SW_SPST_12x12
SW4: mode; SW_SPST_12x12
SW5: wave; SW_SPST_12x12
SW7: RotaryEncoder_Switch; Encoder_EC11
U1: ESP32-S3-DEVKITC-1-N16R8V; PARTREV 1.1
U3: PCM5102A-module
U4: DM-OLED096-636; MODULE_DM-OLED096-636

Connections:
+3.3V: J5.1 (3V3), R1.1, R10.1, U1.J1_1 (3V3), U1.J1_2 (3V3), U4.2 (VCC_IN)
+5V: C1.1, C2.1, J4.1 (VCC), J4.12 (VCC), R6.1, U1.J1_21 (5V0), U3.15 (VIN)
/BCLK: U1.J3_5 (GPIO2), U3.11 (BCK)
/DIN: U1.J3_6 (MTMS/GPIO42), U3.12 (DIN)
/LRCK: U1.J3_7 (MTDI/GPIO41), U3.13 (LRCK)
/SD_CLK: J5.4 (CLK), U1.J3_17 (GPIO47)
/SD_CMD: J5.3 (MOSI/CMD), U1.J3_18 (GPIO21)
/SD_D0: J5.5 (MISO/D0), U1.J3_16 (GPIO48)
GND: C1.2, C2.2, C3.1, J4.6 (GND), J4.7 (GND), J5.6 (GND), R7.2, R8.2, R9.2, SW1.2, SW2.2, SW3.1, SW4.2, SW5.2, SW7.C, SW7.S2, U1.J1_22 (GND), U1.J3_1 (GND), U1.J3_21 (GND), U1.J3_22 (GND), U3.14 (DGND), U4.1 (GND)
unnamed: J2.1, R3.1, U3.9 (LROUT)
unnamed: J2.2, J3.2, R4.2, R5.2, U3.8 (AGND)
unnamed: J2.3, R2.1, U3.7 (ROUT)
unnamed: J3.1, R3.2, R5.1
unnamed: J3.3, R2.2, R4.1
unnamed: J4.2 (CC1), R8.1
unnamed: J4.8 (CC2), R9.1
unnamed: R6.2, R7.1, U1.J3_4 (GPIO1)
unnamed: SW5.1, U1.J1_4 (GPIO4)
unnamed: SW3.2, U1.J1_5 (GPIO5)
unnamed: SW7.S1, U1.J1_6 (GPIO6)
unnamed: SW7.B, U1.J1_7 (GPIO7)
unnamed: SW2.1, U1.J1_19 (GPIO13)
unnamed: SW4.1, U1.J1_20 (GPIO14)
unnamed: SW7.A, U1.J1_8 (GPIO15)
unnamed: SW1.1, U1.J1_9 (GPIO16)
unnamed: U1.J3_9 (MTCK/GPIO39), U4.3 (SCL)
unnamed: U1.J3_8 (MTDO/GPIO40), U4.4 (SDA)
unnamed: C3.2, R10.2, U1.J1_3 (RST)
unnamed: R1.2, U3.10 (SCK)

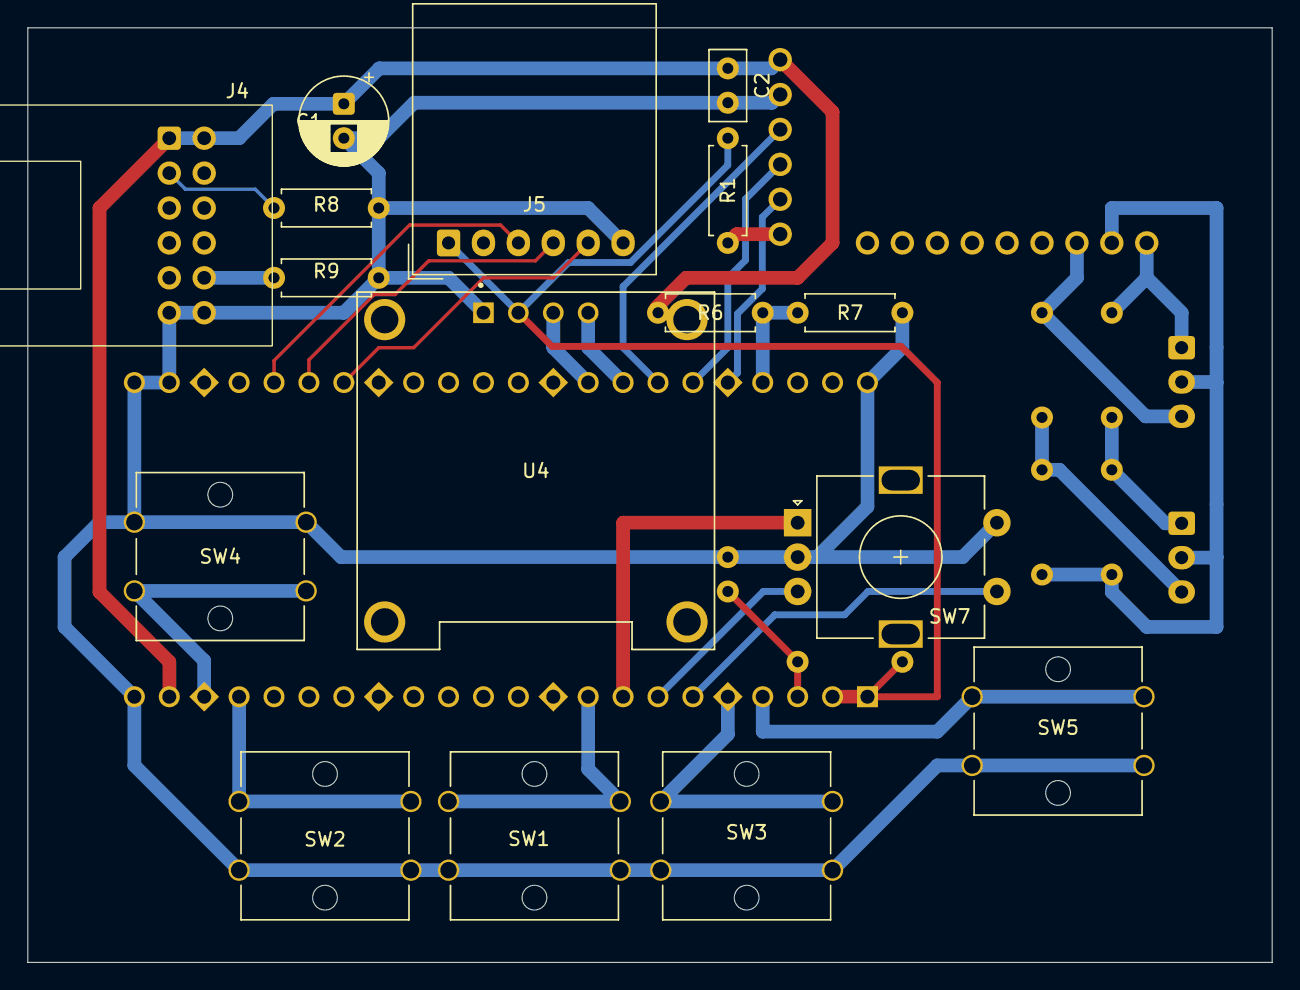
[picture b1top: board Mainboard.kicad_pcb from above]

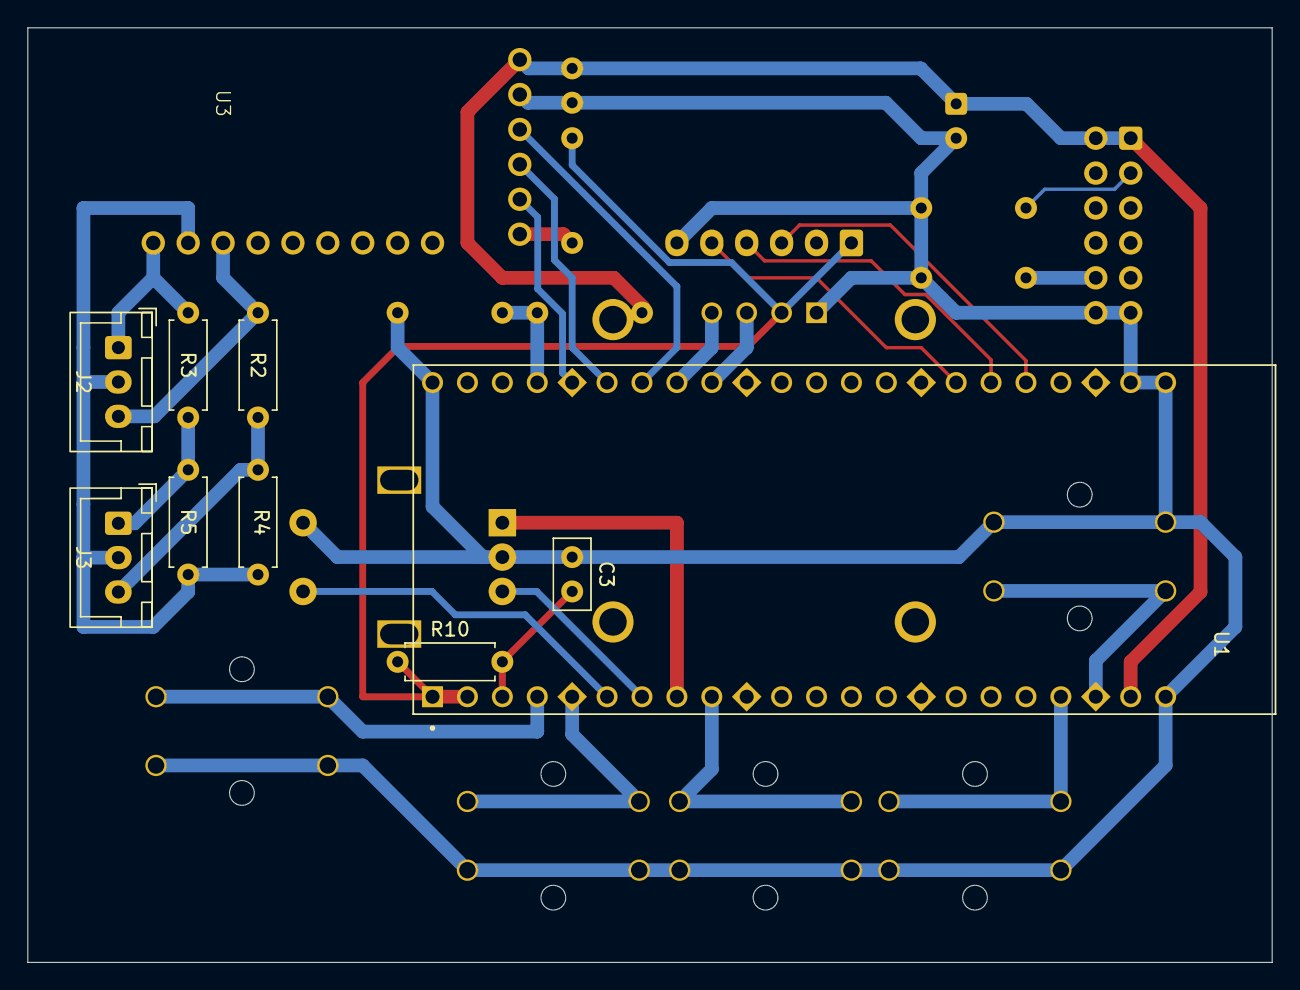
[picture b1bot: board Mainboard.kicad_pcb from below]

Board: 2 copper layers, 90.5 x 68.0 mm, 26 parts (10 on the bottom side), 29 nets.

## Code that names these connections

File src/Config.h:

#pragma once
#include <Arduino.h>

// =============================================================================
// 1. АППАРАТНАЯ КОНФИГУРАЦИЯ (ПИНЫ GPIO)
// =============================================================================
// --- Интерфейс I2S (Звуковой ЦАП PCM5102A) ---
const int BCLK_PIN = 2;
const int LRCK_PIN = 41;
const int DIN_PIN  = 42;

// --- Интерфейс I2C (Дисплей SSD1306) ---
const int SDA_PIN  = 40;
const int SCL_PIN  = 39;

// --- Интерфейс SD-Card ---
const int SD_MMC_D0  = 48;
const int SD_MMC_CLK = 47;
const int SD_MMC_CMD = 21;

// --- Квадратурный энкодер ---
const int PIN_ENC_A    = 7;    // Enc+ (CLK)
const int PIN_ENC_B    = 15;   // Enc- (DT)
const int PIN_ENC_BTN  = 6;    // Enc Btn (Mute / Unmute)

// --- Линейка тактовых кнопок ---
const int PIN_BTN_1    = 16;  // BOTH CH
const int PIN_BTN_2    = 13;  // LEFT CH
const int PIN_BTN_3    = 5;   // RIGHT CH
const int PIN_BTN_4    = 14;  // MODE (STATIC -> SWEEP -> ...)
const int PIN_BTN_5    = 4;   // WAVE (SIN -> SQR)

// =============================================================================
// 2. ИНЖЕНЕРНЫЕ И КОНСТРУКТОРСКИЕ КОНСТАНТЫ
// =============================================================================
const int PHASE_STEP       = 10;    // Шаг изменения фазы в градусах
const double FREQ_MIN      = 0.1;   // Минимальная частота генерации, Гц
const double FREQ_MAX      = 22000.0; // Максимальная частота генерации, Гц
const unsigned long FOCUS_TIMEOUT = 5000; // Таймаут фокуса интерфейса (5 секунд)

// =============================================================================
// 3. ТИПЫ ДАННЫХ И СТРУКТУРЫ СИСТЕМЫ
// =============================================================================

// Глобальные режимы работы каналов
enum ChannelMode {
    MODE_BOTH,   // BOTH CH (Стерео-линк)
    MODE_LEFT,   // SPL CH (Левый в фокусе)
    MODE_RIGHT   // SPL CH (Правый в фокусе)
};

// Подрежимы генерации сигнала
enum SignalSubMode {
    SUBMODE_STATIC,      // FIX (Постоянная частота)
    SUBMODE_SWEEP,       // SWP (Качание частоты)
    SUBMODE_PHASE_SHIFT, // PHASE SHIFT (Ручной статический сдвиг)
    SUBMODE_PHASE_ROT,   // PHASE ROT (Динамическое вращение)
    SUBMODE_IMD,         // IMD TEST (Двухтональный тест искажений)
    SUBMODE_WHITE_NOISE, // Белый шум
    SUBMODE_PINK_NOISE   // Розовый шум
};

// Форма генерируемой волны
enum WaveForm {
    WAVE_SIN,            // Синусоида (SIN)
    WAVE_SQR             // Меандр (SQR)
};

// Структура индивидуальных настроек одного канала
struct ChannelSettings {
    double freq;           // Текущая частота канала в Гц
    WaveForm wave;         // Форма волны канала
    SignalSubMode subMode; // Подрежим генерации (STATIC или SWEEP)
};

// Главная структура состояния прибора
struct DeviceState {
    ChannelMode chMode;         // Текущий режим (BOTH, LEFT, RIGHT)
    ChannelSettings left;       // Настройки левого канала (Master)
    ChannelSettings right;      // Настройки правого канала (Slave)
    
    int phaseAngle;             // Угол сдвига фазы (0...360)
    bool isMute;                // Флаг глушения звука
    int volume;                 // Текущая общая громкость (0...100%)
    
    // Переменные состояния интерфейса (Ядро 0)
    int activeCursorDigit;      // Позиция курсора частоты (-1 — выкл, 0..5 — индекс разряда)
    bool isPhaseFocus;          // Флаг фокуса энкодера на изменении фазы в шапке
    unsigned long focusTimer;   // Время (millis()) последнего действия пользователя
};

struct AppSettings {
    float sweepStartF;
    float sweepStopF;
    float sweepDuration;
    float phaseRotDuration;
    double bootFreq;
    int bootLevelDb;
    int startScreen;            // 0=Main, 1=Waves, 2=Noises, 3=MP3
    float imdFreq1;             // Первая частота интермодуляции (например, 60.0f)
    float imdFreq2;             // Вторая частота интермодуляции  (например, 7000.0f)
    float imdRatio1;            // Коэффициент амплитуды первой частоты (например, 0.8f для 4/5)
    float imdRatio2;            // Коэффициент амплитуды второй частоты (например, 0.2f для 1/5)
    bool playModeLoop;
};

// =============================================================================
// 4. ГЛОБАЛЬНЫЕ ПЕРЕМЕННЫЕ (ОБЪЯВЛЕНИЕ)
// =============================================================================
// Использование extern гарантирует, что объект dev будет создан в одном месте (в .ino файле),
// но доступен для чтения и записи во всех модулях (.cpp).


extern DeviceState dev;
extern AppSettings cfg;

void config_load();
void config_save();
